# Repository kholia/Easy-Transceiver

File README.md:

### Easy-Transceiver

The whole design is modular, parametric (cost and others), field repairable,
and super extensible. It is almost trivial to add support for more `FSK digital
modes`.

The `Easy-Transceiver` hardware works with the native `Hybrid FT8 Radio`
Android app, and also with WSJT-X (running on RPi).

The `Easy-Transceiver` system can be built for around 3000 INR (~40 USD) or
less. We are working on reducing the cost to 2300 INR ;)

Author 1: LU2HES - https://github.com/agustinmartino

Author 2: Dhiru Kholia (VU3CER) - https://www.qrz.com/db/VU3CER/

TX chain:

RX chain (Easy-uSDX - optionally headless):

QSO(s):

QSOs over 15000 kms were made using this HW with PA150 (with around 37W ERP).

#### Notes

This will need a HF RF PA in most cases to be usable on the air.

UPDATE (January 2022): Check out our [cost-effective, and robust HF PA system](https://github.com/kholia/HF-PA-v5/).

#### Setup

- Use Python 3.10.x for maximum compatibility.

- Setup dependencies.

  `pip install -r requirements.txt`

#### T/R Switch

Check out our [cost-effective, and simple T/R switch design](https://github.com/kholia/Simple-TR-Switch/).

#### BCI Filter

Are you hearing broadcast AM signals in the background of the uSDX receiver? If
yes, a simple `BCI filter` can solve this problem easily enough.

Checkout the [RX BCI Filter](./HPF-BCI-Filter-RX) included in this repository.

#### BOM

- High Quality Female to Female Jumper Wire - 2500mA (Project Point)

- Female and male berg strip

- Arduino Nano v3 board - 450 INR - We will eliminate this requirement soon

- SN74CB3T3253DR (SOIC-16, Semikart) - ~200 INR

- Bunch of 100nF MLCC - 25 INR ('Emerging Technologies' Store -> ET)

- Bunch of 10nF MLCC - 10 INR

- Bunch of 1nF MLCC - 20 INR

- 4 x 470nF MLCC - 10 INR

- 1 x 1N5819 - 2 INR

- 1 x 1N4007 - 2 INR

- 1 x 7805 Linear Regulator - 15 INR

- 2 x 100uH inductor - 12 INR

- Si5351 Module - 470 INR (no delicate soldering required!)

  - Cheaper to get MS5351M from LCSC (in bulk for more experiments) - <= 100 INR

- Bunch of 10k resistors (MFR, ET / Project Point) - 25 INR

- Bunch of 1k resistors - 10 INR

- 1 x 1k 0.5W resistor - 5 INR

- 1 x 470 0.25W resistor - 5 INR

- 2 x 82k 0.25 resistor (MFR) - 5 INR

- 4 x 100 Ohm resistor (MFR) - 5 INR

- 1 x 3.5mm Stereo Socket ('PJ-307', https://www.electroncomponents.com/Stereo-Socket-3.5mm-connector-pcb) - 12 INR

- BCI Filter BOM - 2 x 2.2nF ceramic capacitor, 2 x 820pF (can be resistor shaped!), 3 * 2.2uH inductor axial

- 2 x SMA connectors (https://www.ktron.in/, SMA Straight - Female - Vertical Mount) - 50 INR

- ATmega328P (DIP-28) - 225 INR

- 20 MHz crystal - 10 INR

- LM4562NA - 220 INR (Semikart) OR NE5532AP (130 INR from Semikart, 30 INR locally from https://rarecomponents.com)

  The `NE5532` is widely faked - even https://www.electronicscomp.com/ sells a cheap knockoff!

  TIP: Get `TI make NE5532` from https://rarecomponents.com/.

- Misc: Copper clad board (glass epoxy one), Relimate male connectors + female
  cable, Male berg strip, Female-to-female dupont cables

  Get from https://www.electronicscomp.com/ and https://projectpoint.in/ shops.

- Total: Around 1500 to 1600 INR

#### BOM Sources

- https://robu.in/ (https://www.ktron.in/ has better pricing at times)

- https://www.electronicscomp.com/ (2.2uH Inductor)

- https://projectpoint.in/ (222 MLCC, 820pF MLCC)

- https://www.electroncomponents.com/2.2uh-inductor-inductance-coil (2.2uH Inductor)

#### Tips

Useful commands:

```
pacmd load-module module-null-sink sink_name=Virtual0
pacmd update-sink-proplist Virtual0 device.description=Virtual0
pacmd update-source-proplist Virtual0.monitor device.description=Virtual0
```

Use Gqrx and WSJT-X with a SDR device for initial frequency adjustment /
calibration. This is essential for WSPR functionality. FT8 is more
robust/tolerant of frequency deviations due to a much larger RX window.

#### References + Credits

- https://github.com/WB2CBA for the uSDX PCB

- https://github.com/kgoba/ft8_lib

- https://github.com/etherkit/JTEncode

- https://learn.adafruit.com/adafruit-si5351-clock-generator-breakout/wiring-and-test

- https://github.com/agustinmartino/wsjt_transceiver

- https://github.com/agustinmartino/wsjtx_transceiver_interface

- https://www.qrp-labs.com/synth/ms5351m.html

- https://github.com/kholia/Easy-Digital-Beacons-v1

- https://github.com/kholia/HF-Balcony-Antenna-System (fun!)

- https://github.com/kholia/SMPS-Noise-Filter

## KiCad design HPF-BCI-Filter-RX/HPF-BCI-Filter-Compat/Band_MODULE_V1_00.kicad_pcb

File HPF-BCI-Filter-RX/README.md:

Credits: https://www.youtube.com/watch?v=fgQenFJOjr4 (VK3YE)

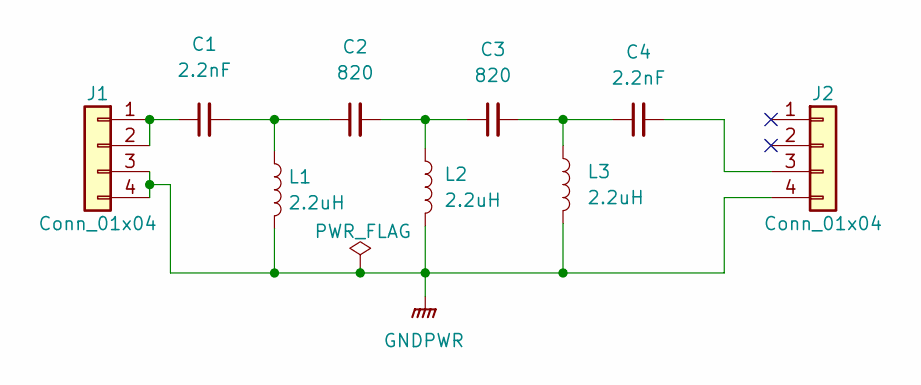
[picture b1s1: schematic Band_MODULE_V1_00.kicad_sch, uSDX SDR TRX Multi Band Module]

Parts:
C1, C4: 2.2nF; C_Disc_D3.0mm_W1.6mm_P2.50mm
C2, C3: 820; C_Disc_D3.0mm_W1.6mm_P2.50mm
J1, J2: Conn_01x04; PinHeader_1x4_P2.54mm_Drill1.02mm; MPN 0022232041; Digi-Key_PN WM4202-ND
L1, L2, L3: 2.2uH; R_Axial_DIN0204_L3.6mm_D1.6mm_P1.90mm_Vertical

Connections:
GNDPWR: J1.3, J1.4, J2.4, L1.2, L2.2, L3.2
unnamed: C1.1, J1.1, J1.2
unnamed: C1.2, C2.1, L1.1
unnamed: C2.2, C3.1, L2.1
unnamed: C3.2, C4.1, L3.1
unnamed: C4.2, J2.3

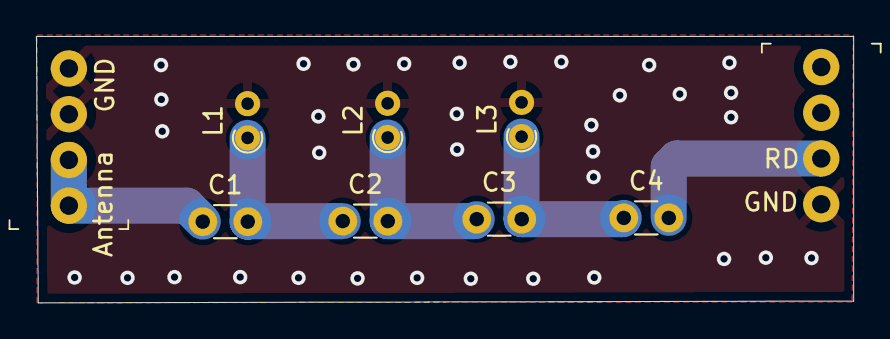
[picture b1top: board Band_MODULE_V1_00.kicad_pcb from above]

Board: 2 copper layers, 45.4 x 14.8 mm, 9 parts (0 on the bottom side), 6 nets.

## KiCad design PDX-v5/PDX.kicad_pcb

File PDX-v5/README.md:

#### PDX

A port of https://github.com/WB2CBA/ADX/ to Raspberry Pi Pico.

PDX-v3 is like v2 but is adapted for manufacturing @ JLCPCB.

PDX-v4 is like v3 with minor bugfixes.

PDX-v5 is like v4 with ADC-voltage-limiting circuit.

Bands covered: 80-meter to 15-meter.

FT8 is natively decoded on the Pico using the code from the following
repository:

https://github.com/kholia/pico_ft8_xcvr

The `PDX RX Block` when combined with the following project becomes a complete
5W (to 10W!) digital FT8 transceiver.

- https://github.com/kholia/HF-PA-v6/tree/master/HF-PA-Combined

  Solid 3W+ on 15m, 6W+ on 20m, 10W+ on 40m band. All @ 13.8v only!

  Set high gate bias (even 4.2v!) for IRF510 for clean linear output.

The live FT8 audio can also be decoded on PC / RPi / Android phone.

#### BOM Sources

International users can buy from Mouser and DigiKey.

Here are some local BOM sources I use:

- https://inkocean.in/ - CD2003 (Chinese clone which is known to work fine)

- https://www.electronicscomp.com/ (SMD resistors + SMD caps + THT inductors)

  - All SMD caps and resistors are 1206 sized

- https://www.ktron.in/ (SMA connectors)

- https://www.comkey.in/ - Branded SMD stuff

- https://rarecomponents.com/store/1002 - NXP 1N4148

- https://projectpoint.in/ - CDIL 7805, PJ307 Stereo Socket

- https://www.evelta.com/l7805-positive-voltage-regulator-1-5a-5v/ (alternate)

- https://robu.in/product/si5351a-i2c-8-khz-160-mhz-clock-generator-breakout-board-module/

- https://robu.in/product/raspberry-pi-pico/

- https://etstore.in/ - OEN MICRO RELAY 46-05-2C

#### Credits

- https://github.com/WB2CBA/ADX/

- https://www.qrz.com/DB/VU2BGS

#### References

- https://f5npv.wordpress.com/homebrew-ft8qrp-afp-fsk-trx/

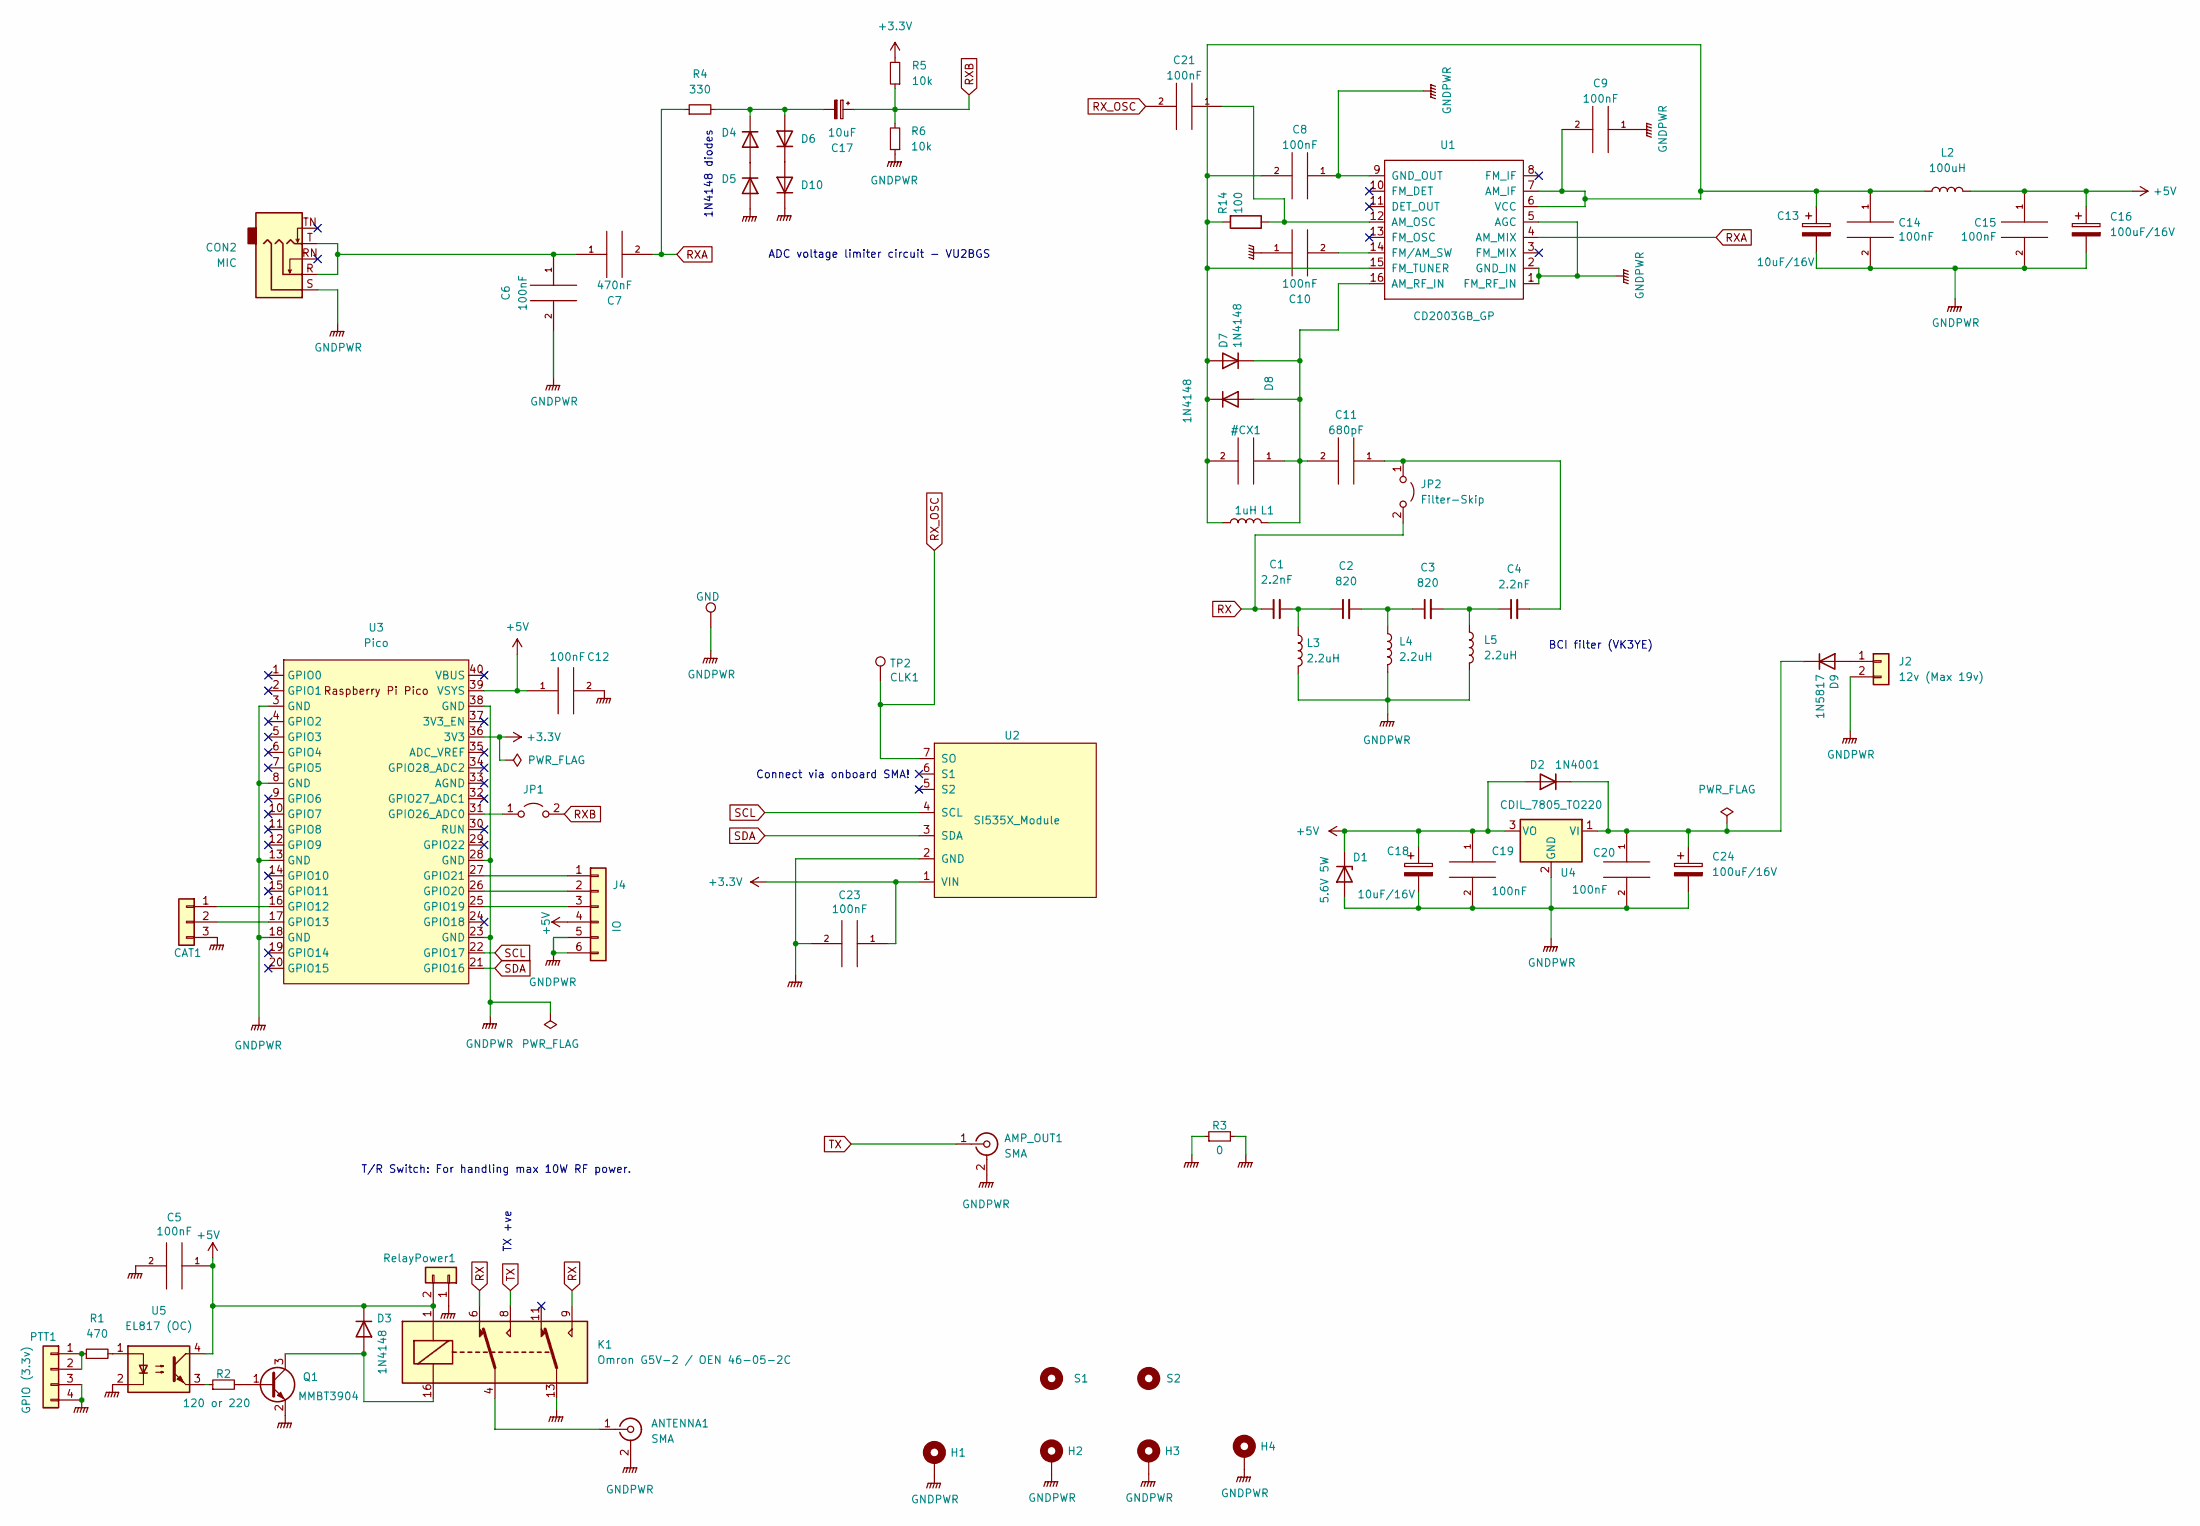
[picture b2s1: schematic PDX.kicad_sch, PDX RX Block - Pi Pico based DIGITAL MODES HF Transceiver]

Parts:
AMP_OUT1: SMA; SMA_Amphenol_901-144_Vertical
ANTENNA1: SMA; SMA_Amphenol_901-144_Vertical
C1, C4: 2.2nF; C_1206_3216Metric_Pad1.33x1.80mm_HandSolder
C2, C3: 820; C_1206_3216Metric_Pad1.33x1.80mm_HandSolder
C5, C6, C8, C9, C10, C12, C14, C15, C19, C20, C21, C23: 100nF; C_1206_3216Metric_Pad1.33x1.80mm_HandSolder
C7: 470nF; C_1206_3216Metric_Pad1.33x1.80mm_HandSolder
C11: 680pF; C_1206_3216Metric_Pad1.33x1.80mm_HandSolder
C13, C18: 10uF/16V; CP_Radial_D4.0mm_P2.00mm
C16, C24: 100uF/16V; CP_Radial_D4.0mm_P2.00mm
C17: 10uF; CP_Radial_D4.0mm_P2.00mm
CAT1: CAT; PinHeader_1x03_P2.54mm_Vertical
CON2: MIC; PJ-307
D1: 5.6V 5W; D_DO-15_P5.08mm_Vertical_KathodeUp
D2: 1N4001; D_SMA_Handsoldering
D3, D4, D5, D6, D7, D8, D10: 1N4148; D_DO-35_SOD27_P2.54mm_Vertical_KathodeUp
D9: 1N5817; D_A-405_P2.54mm_Vertical_KathodeUp
H1, H2, H3, H4: MountingHole_Pad; MountingHole_3.2mm_M3_ISO7380_Pad
J2: 12v (Max 19v); PinHeader_1x02_P2.54mm_Vertical
J4: IO; PinHeader_1x06_P2.54mm_Vertical
JP1: Jumper_2_Open; PinHeader_1x02_P2.54mm_Vertical
JP2: Filter-Skip; PinHeader_1x02_P2.54mm_Vertical
K1: Omron G5V-2 / OEN 46-05-2C; Relay_DPDT_Omron_G5V-2
L1: 1uH; L_Axial_L5.3mm_D2.2mm_P2.54mm_Vertical_Vishay_IM-1
L2: 100uH; L_Axial_L5.3mm_D2.2mm_P2.54mm_Vertical_Vishay_IM-1
L3, L4, L5: 2.2uH; L_Axial_L5.3mm_D2.2mm_P2.54mm_Vertical_Vishay_IM-1
PTT1: GPIO (3.3v); PinHeader_1x04_P2.54mm_Vertical
Q1: MMBT3904; SOT-23
R1: 470; R_1206_3216Metric_Pad1.30x1.75mm_HandSolder
R2: 120 or 220; R_1206_3216Metric_Pad1.30x1.75mm_HandSolder
R3: 0; R_1206_3216Metric_Pad1.30x1.75mm_HandSolder
R4: 330; R_1206_3216Metric_Pad1.30x1.75mm_HandSolder
R5, R6: 10k; R_Axial_DIN0207_L6.3mm_D2.5mm_P2.54mm_Vertical
R14: 100; R_1206_3216Metric_Pad1.30x1.75mm_HandSolder
RELAY_POWER1: RelayPower1; PinHeader_1x02_P2.54mm_Vertical
S1, S2: MountingHole; MountingHole_2.7mm_M2.5
TP2: CLK1; PinHeader_1x01_P2.54mm_Vertical
TP7: GND; PinHeader_1x01_P2.54mm_Vertical
U1: CD2003GB_GP; DIP-16_W7.62mm_Socket
U2: SI535X_Module; PinSocket_1x07_P2.54mm_Vertical
U3: Pico; RPi_Pico_SMD_TH
U4: CDIL_7805_TO220; TO-220-3_Vertical
U5: EL817 (OC); DIP-4_W7.62mm

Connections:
+3V3: C23.1, R5.2, U2.1 (VIN), U3.36 (3V3)
+5V: C5.1, C12.1, C15.1, C16.1, C18.1, C19.1, D1.1 (K), D2.2 (A), D3.1 (K), J4.4, K1.1, L2.2, RELAY_POWER1.2, U3.39 (VSYS), U4.3 (VO), U5.4
GNDPWR: AMP_OUT1.2 (Ext), ANTENNA1.2 (Ext), C5.2, C6.2, C8.1, C9.1, C10.1, C12.2, C13.2, C14.2, C15.2, C16.2, C18.2, C19.2, C20.2, C23.2, C24.2, CAT1.3, CON2.S, D1.2 (A), D5.2 (A), D10.1 (K), H1.1, H2.1, H3.1, H4.1, J2.2, J4.5, J4.6, K1.13, L3.2, L4.2, L5.2, PTT1.3, PTT1.4, Q1.2 (E), R3.1, R3.2, R6.1, RELAY_POWER1.1, TP7.1, U1.1 (FM_RF_IN), U1.2 (GND_IN), U1.5 (AGC), U1.9 (GND_OUT), U2.2 (GND), U3.3 (GND), U3.8 (GND), U3.13 (GND), U3.18 (GND), U3.23 (GND), U3.28 (GND), U3.38 (GND), U4.2 (GND), U5.2
unnamed: ANTENNA1.1 (In), K1.4
unnamed: C1.2, C2.1, L3.1
unnamed: C2.2, C3.1, L4.1
unnamed: C3.2, C4.1, L5.1
unnamed: C6.1, C7.1, CON2.R, CON2.T
unnamed: C10.2, U1.14 (FM/AM_SW)
unnamed: C4.2, C11.1, JP2.1 (A)
unnamed: C17.2, D4.1 (K), D6.2 (A), R4.2
unnamed: C20.1, C24.1, D2.1 (K), D9.1 (K), U4.1 (VI)
unnamed: C21.1, R14.1, U1.12 (AM_OSC)
unnamed: CAT1.1, U3.16 (GPIO12)
unnamed: CAT1.2, U3.17 (GPIO13)
unnamed: D3.2 (A), K1.16, Q1.3 (C)
unnamed: D4.2 (A), D5.1 (K)
unnamed: D9.2 (A), J2.1
unnamed: D6.1 (K), D10.2 (A)
unnamed: J4.1, U3.27 (GPIO21)
unnamed: J4.2, U3.26 (GPIO20)
unnamed: J4.3, U3.25 (GPIO19)
unnamed: JP1.1 (A), U3.31 (GPIO26_ADC0)
unnamed: PTT1.1, PTT1.2, R1.1
unnamed: Q1.1 (B), R2.2
unnamed: R1.2, U5.1
unnamed: R2.1, U5.3
RX: C1.1, JP2.2 (B), K1.6, K1.9
RXA: C7.2, R4.1, U1.4 (AM_MIX)
RXB: C17.1, JP1.2 (B), R5.1, R6.2
RX_OSC: C21.2, TP2.1, U2.7 (SO)
SCL: U2.4 (SCL), U3.22 (GPIO17)
SDA: U2.3 (SDA), U3.21 (GPIO16)
TX: AMP_OUT1.1 (In), K1.8

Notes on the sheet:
Connect via onboard SMA!
BCI filter (VK3YE)
1N4148 diodes
T/R Switch: For handling max 10W RF power.
ADC voltage limiter circuit - VU2BGS
TX +ve

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
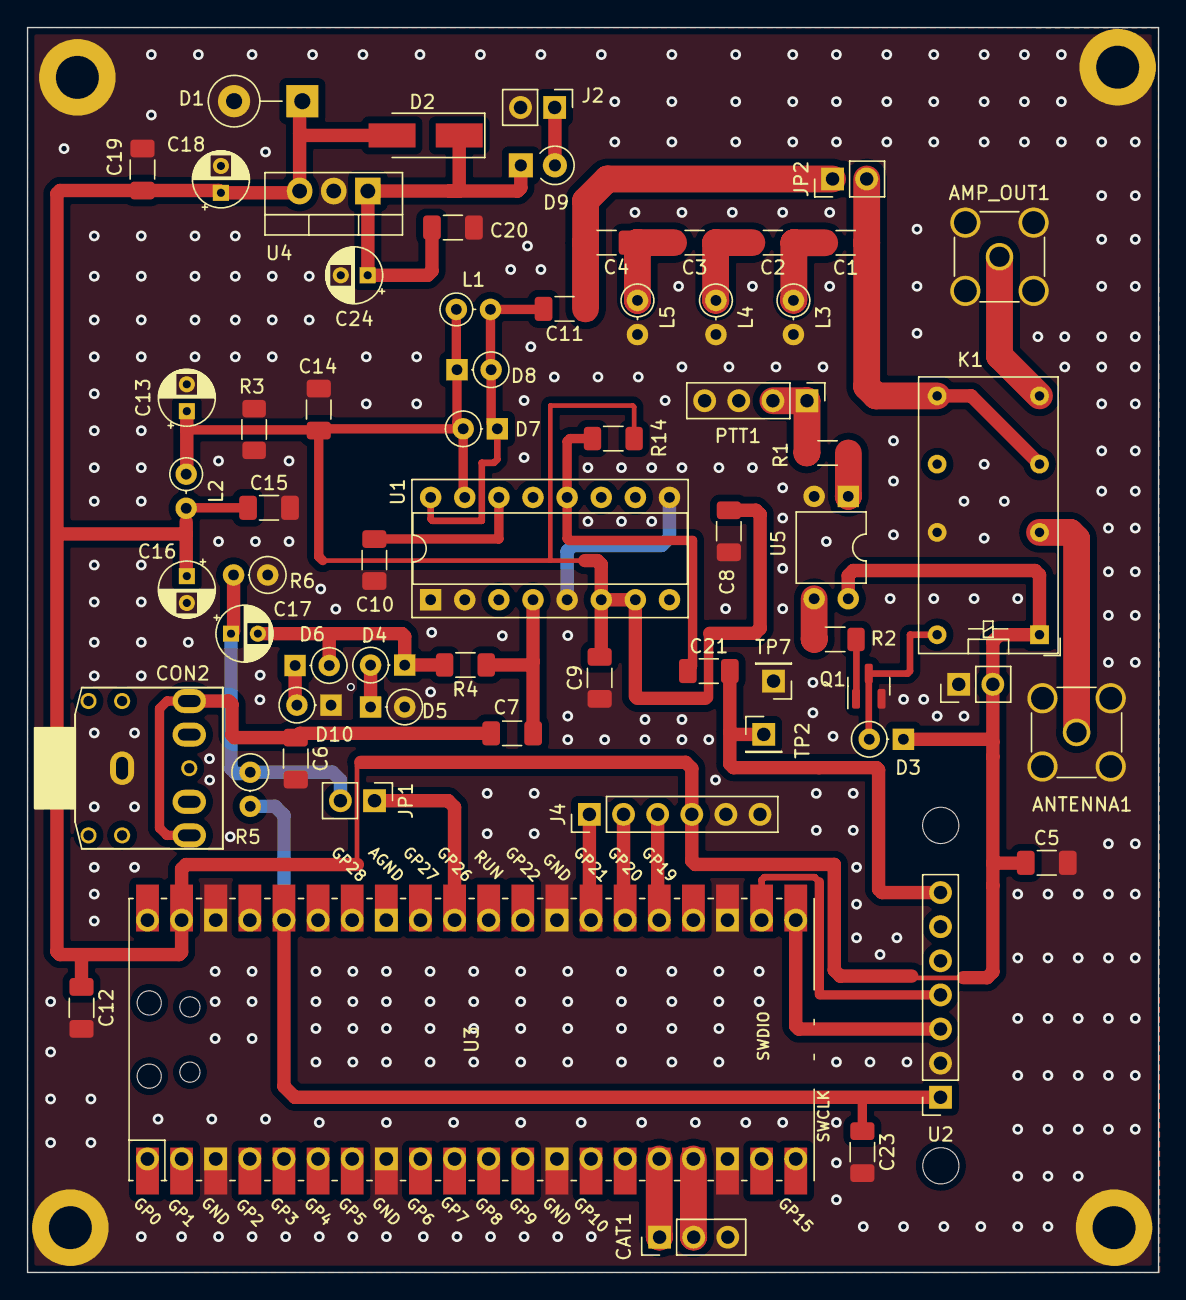
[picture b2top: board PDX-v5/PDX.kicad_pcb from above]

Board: 2 copper layers, 84.2 x 92.7 mm, 70 parts (0 on the bottom side), 36 nets.

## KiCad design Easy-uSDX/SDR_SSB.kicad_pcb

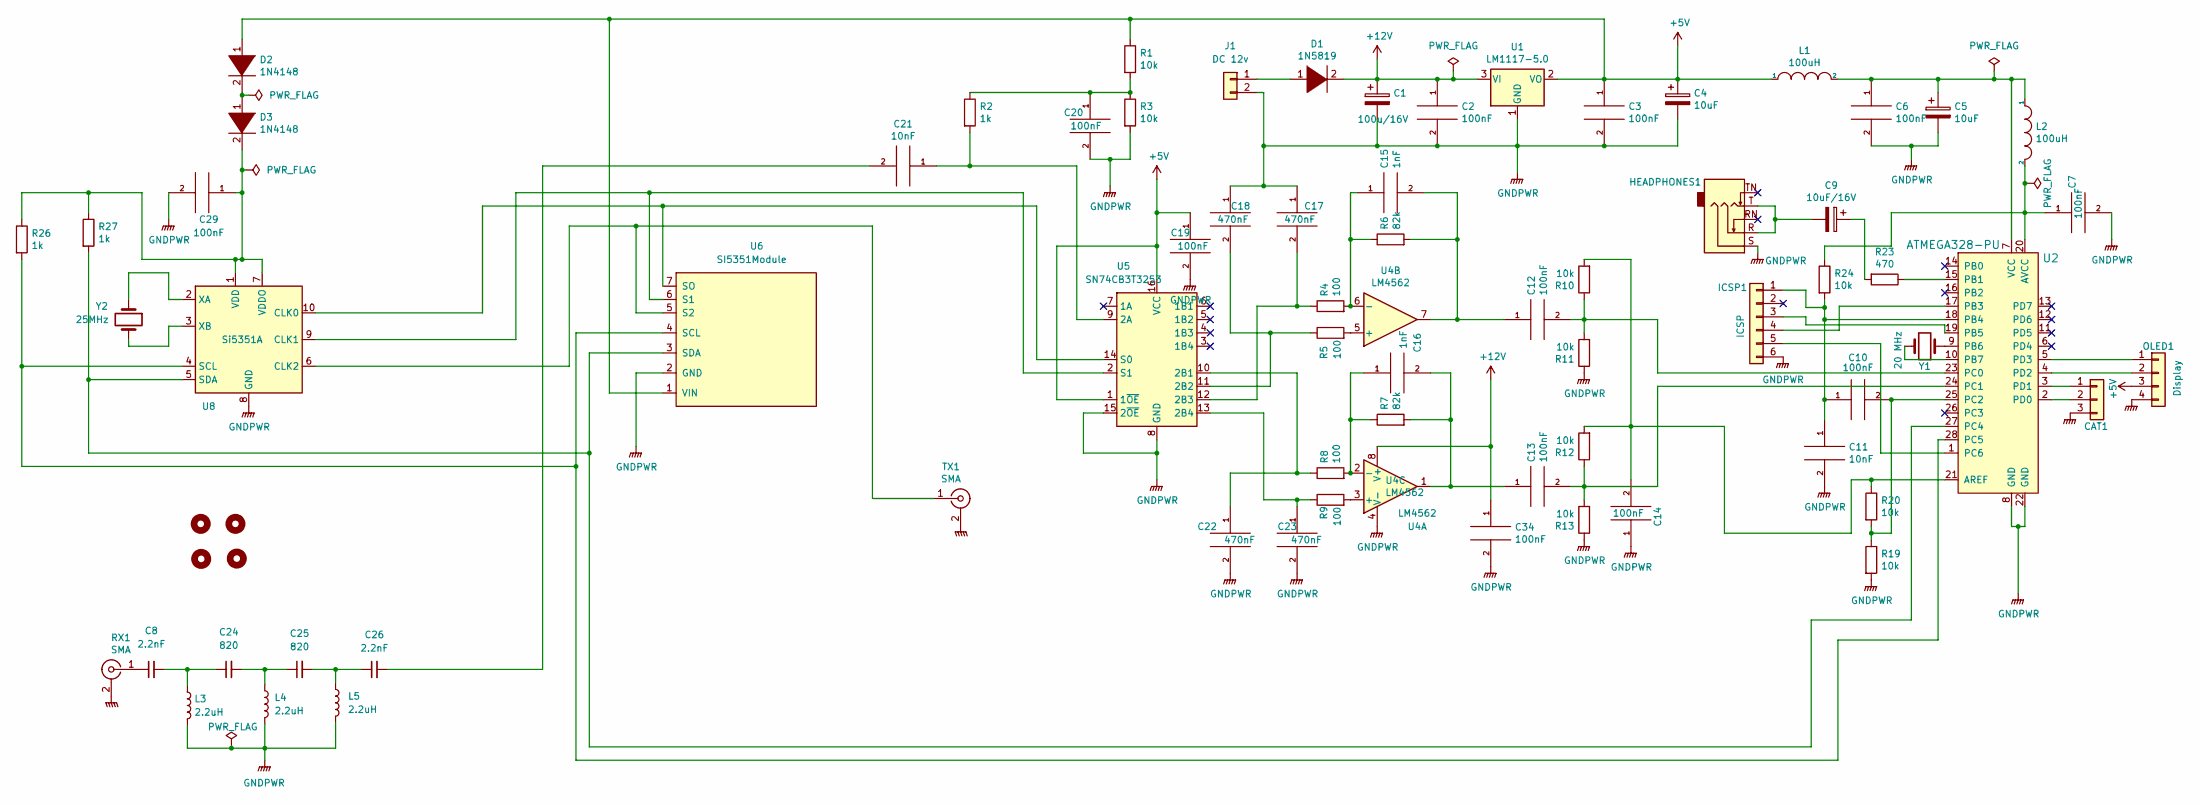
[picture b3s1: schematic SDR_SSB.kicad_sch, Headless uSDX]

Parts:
C1: 100u/16V; CP_Radial_D5.0mm_P2.50mm
C2, C3, C6, C7, C10, C12, C13, C14, C19, C20, C29, C34: 100nF; C_Disc_D3.0mm_W2.0mm_P2.50mm
C4, C5: 10uF; CP_Radial_D4.0mm_P2.00mm
C8, C26: 2.2nF; C_Disc_D3.0mm_W1.6mm_P2.50mm
C9: 10uF/16V; CP_Radial_D4.0mm_P2.00mm
C11, C21: 10nF; C_Disc_D3.0mm_W2.0mm_P2.50mm
C15, C16: 1nF; C_Disc_D3.0mm_W2.0mm_P2.50mm
C17, C18, C22, C23: 470nF; C_Disc_D3.0mm_W2.0mm_P2.50mm
C24, C25: 820; C_Disc_D3.0mm_W1.6mm_P2.50mm
CAT1: CAT; PinHeader_1x03_P2.54mm_Vertical
D1: 1N5819; D_A-405_P2.54mm_Vertical_AnodeUp
D2, D3: 1N4148; D_DO-35_SOD27_P2.54mm_Vertical_KathodeUp
H1, H2, H3, H4: MountingHole; MountingHole_2.2mm_M2
HEADPHONES1: AudioJack3_SwitchTR; PJ-307
ICSP1: ICSP; PinHeader_2x03_P2.54mm_Vertical
J1: DC 12v; PinHeader_1x02_P2.54mm_Vertical
L1, L2: 100uH; L_Axial_L5.3mm_D2.2mm_P2.54mm_Vertical_Vishay_IM-1
L3, L4, L5: 2.2uH; R_Axial_DIN0204_L3.6mm_D1.6mm_P1.90mm_Vertical
OLED1: Display; PinHeader_1x04_P2.54mm_Vertical
R1, R3, R10, R11, R12, R13, R19, R20, R24: 10k; R_Axial_DIN0204_L3.6mm_D1.6mm_P1.90mm_Vertical
R2, R26, R27: 1k; R_Axial_DIN0204_L3.6mm_D1.6mm_P1.90mm_Vertical
R4, R5, R8, R9: 100; R_Axial_DIN0204_L3.6mm_D1.6mm_P1.90mm_Vertical
R6, R7: 82k; R_Axial_DIN0204_L3.6mm_D1.6mm_P1.90mm_Vertical
R23: 470; R_Axial_DIN0204_L3.6mm_D1.6mm_P1.90mm_Vertical
RX1: SMA; SMA_Amphenol_901-144_Vertical
TX1: SMA; SMA_Amphenol_901-144_Vertical
U1: LM1117-5.0; SOT-223-3_TabPin2
U2: ATMEGA328-PU; DIP-28_W7.62mm_Socket_LongPads; MPN ATMEGA328-PU; Digi-Key_PN ATMEGA328-PU-ND
U4: LM4562; DIP-8_W7.62mm_LongPads
U5: SN74CB3T3253; SOIC-16_4.55x10.3mm_P1.27mm
U6: SI5351Module; SI5351 Module
U8: Si5351A; MSOP-10_3x3mm_P0.5mm
Y1: 20 MHz; Crystal_HC49-U_Vertical
Y2: 25MHz; Crystal_HC49-U_Vertical

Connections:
+5V: C3.1, C4.1, C19.1, D2.1 (K), L1.1, OLED1.3, R1.1, U1.2 (VO), U5.1 (1~OE), U5.16 (VCC), U6.1 (VIN)
+12V: C1.1, C2.1, C34.1, D1.2 (A), U1.3 (VI), U4.8 (V+)
GNDPWR: C1.2, C2.2, C3.2, C4.2, C5.2, C6.2, C7.2, C11.2, C14.1, C17.1, C18.1, C19.2, C20.2, C22.2, C23.2, C29.2, C34.2, CAT1.3, HEADPHONES1.S, ICSP1.6, J1.2, L3.2, L4.2, L5.2, OLED1.4, R3.2, R11.1, R13.1, R19.2, RX1.2 (Ext), TX1.2 (Ext), U1.1 (GND), U2.8 (GND), U2.22 (GND), U4.4 (V-), U5.8 (GND), U5.15 (2~OE), U6.2 (GND), U8.8 (GND)
unnamed: C5.1, C6.1, L1.2, L2.1, U2.7 (VCC)
unnamed: C7.1, L2.2, R24.1, U2.20 (AVCC)
unnamed: C8.1, RX1.1 (In)
unnamed: C9.1, R23.2
unnamed: C9.2, HEADPHONES1.R, HEADPHONES1.T
unnamed: C10.1, C11.1, ICSP1.1, R24.2, U2.18 (PB4)
unnamed: C10.2, R19.1, R20.2, U2.25 (PC2)
unnamed: C12.1, C15.2, R6.2, U4.7
unnamed: C12.2, R10.1, R11.2, U2.23 (PC0)
unnamed: C13.1, C16.2, R7.2, U4.1
unnamed: C13.2, R12.1, R13.2, U2.24 (PC1)
unnamed: C14.2, R10.2, R12.2, R20.1, U2.21 (AREF)
unnamed: C15.1, R4.2, R6.1, U4.6 (-)
unnamed: C16.1, R7.1, R8.2, U4.2 (-)
unnamed: C17.2, R4.1, U5.12 (2B3)
unnamed: C18.2, R5.1, U5.11 (2B2)
unnamed: C20.1, R1.2, R2.1, R3.1
unnamed: C21.1, R2.2, U5.9 (2A)
unnamed: C21.2, C26.2
unnamed: C22.1, R8.1, U5.10 (2B1)
unnamed: C23.1, R9.1, U5.13 (2B4)
unnamed: C8.2, C24.1, L3.1
unnamed: C24.2, C25.1, L4.1
unnamed: C25.2, C26.1, L5.1
unnamed: C29.1, D3.2 (A), R26.1, R27.1, U8.1 (VDD), U8.7 (VDDO)
unnamed: CAT1.1, U2.3 (PD1)
unnamed: CAT1.2, U2.2 (PD0)
unnamed: D1.1 (K), J1.1
unnamed: D2.2 (A), D3.1 (K)
unnamed: ICSP1.3, U2.19 (PB5)
unnamed: ICSP1.4, U2.17 (PB3)
unnamed: ICSP1.5, U2.1 (PC6)
unnamed: OLED1.1, U2.5 (PD3)
unnamed: OLED1.2, U2.4 (PD2)
unnamed: R5.2, U4.5 (+)
unnamed: R9.2, U4.3 (+)
unnamed: R23.1, U2.15 (PB1)
unnamed: R26.2, U2.28 (PC5), U6.4 (SCL), U8.4 (SCL)
unnamed: R27.2, U2.27 (PC4), U6.3 (SDA), U8.5 (SDA)
unnamed: TX1.1 (In), U6.5 (S2), U8.6 (CLK2)
unnamed: U2.9 (PB6), Y1.1
unnamed: U2.10 (PB7), Y1.2
unnamed: U5.2 (S1), U6.6 (S1), U8.9 (CLK1)
unnamed: U5.14 (S0), U6.7 (SO), U8.10 (CLK0)
unnamed: U8.2 (XA), Y2.1
unnamed: U8.3 (XB), Y2.2

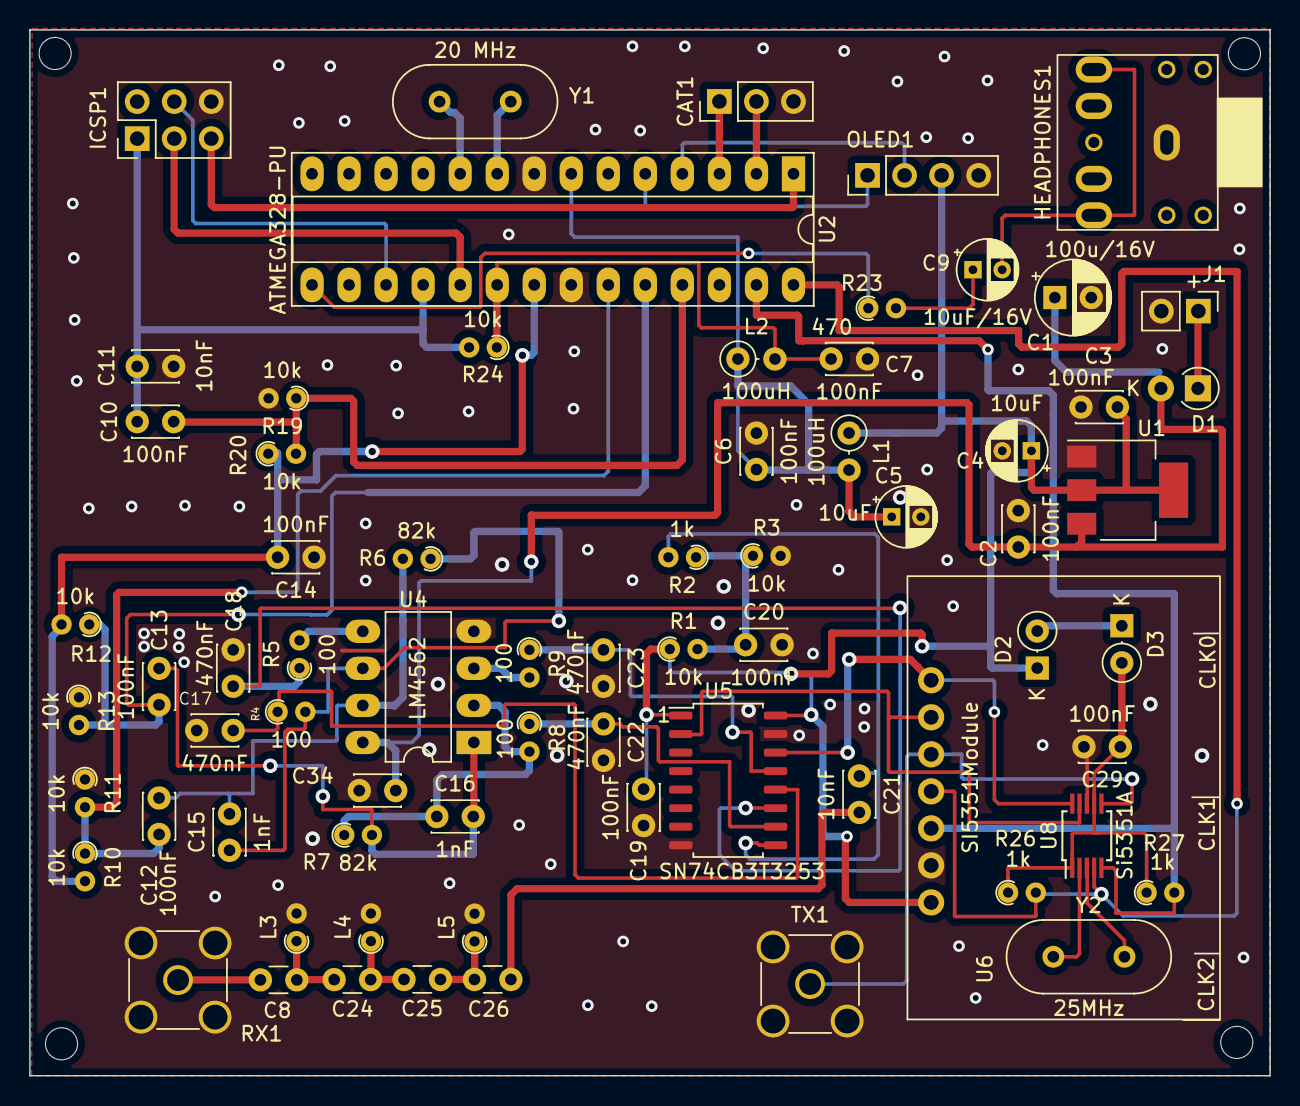
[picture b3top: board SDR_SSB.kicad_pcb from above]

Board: 2 copper layers, 85.1 x 71.7 mm, 74 parts (0 on the bottom side), 49 nets.

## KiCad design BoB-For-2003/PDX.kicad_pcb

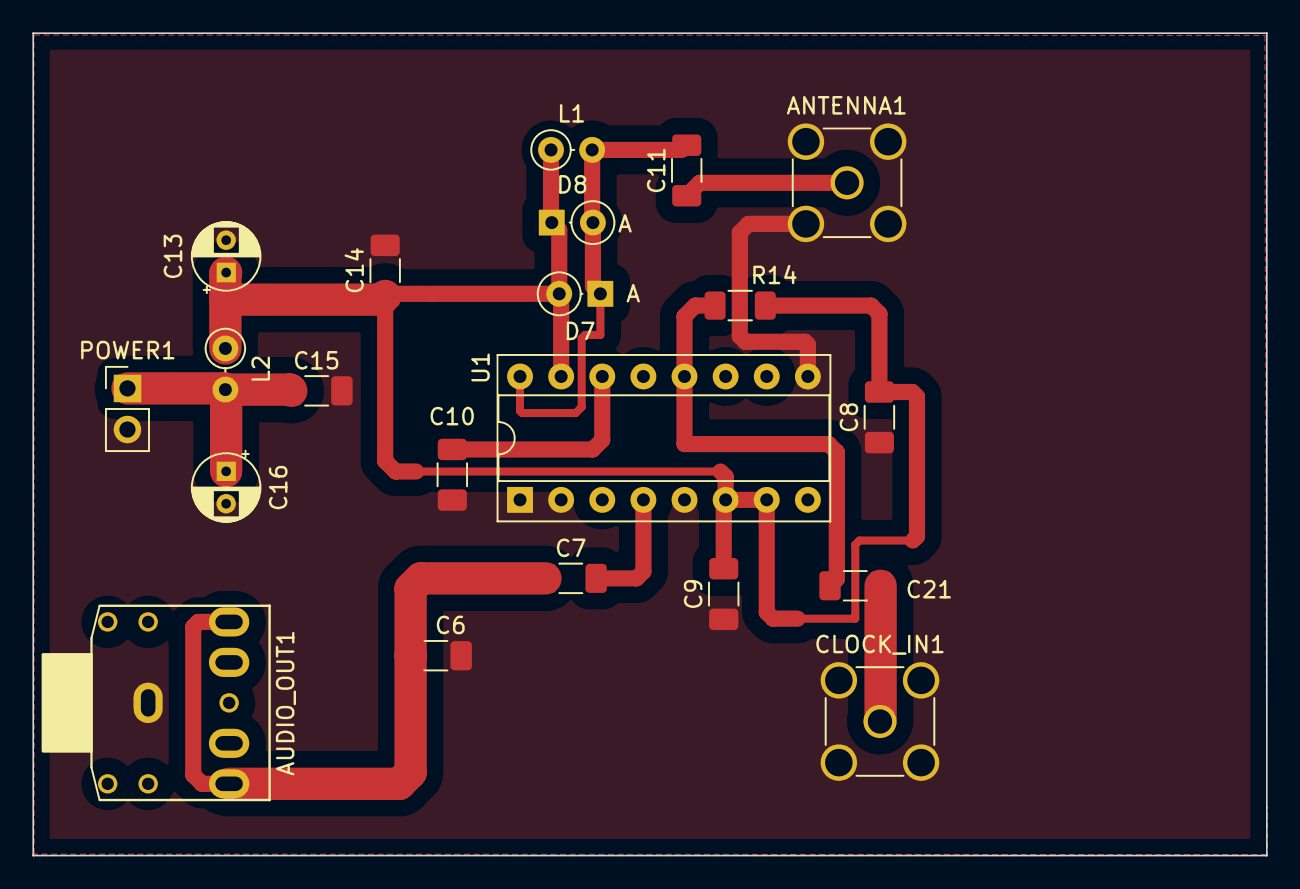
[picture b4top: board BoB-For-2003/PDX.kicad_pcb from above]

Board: 2 copper layers, 76.2 x 50.8 mm, 21 parts (0 on the bottom side), 10 nets.

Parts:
ANTENNA1: RX_INPUT; SMA_Amphenol_901-144_Vertical
AUDIO_OUT1: MIC; PJ-307
C6, C8, C9, C10, C14, C15, C21: 100nF; C_1206_3216Metric_Pad1.33x1.80mm_HandSolder
C7: 470nF; C_1206_3216Metric_Pad1.33x1.80mm_HandSolder
C11: 680pF; C_1206_3216Metric_Pad1.33x1.80mm_HandSolder
C13: 10uF/16V; CP_Radial_D4.0mm_P2.00mm
C16: 100uF/16V; CP_Radial_D4.0mm_P2.00mm
CLOCK_IN1: Conn_Coaxial; SMA_Amphenol_901-144_Vertical
D7, D8: 1N4148; D_DO-35_SOD27_P2.54mm_Vertical_KathodeUp
L1: 1uH; L_Axial_L5.3mm_D2.2mm_P2.54mm_Vertical_Vishay_IM-1
L2: 100uH; L_Axial_L5.3mm_D2.2mm_P2.54mm_Vertical_Vishay_IM-1
POWER1: Conn_01x02; PinHeader_1x02_P2.54mm_Vertical
R14: 100; R_1206_3216Metric_Pad1.30x1.75mm_HandSolder
U1: CD2003GB_GP; DIP-16_W7.62mm_Socket

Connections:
+5V: C15.1, C16.1, L2.2, POWER1.1
GNDPWR: ANTENNA1.2 (Ext), AUDIO_OUT1.S, C6.2, C8.1, C9.1, C10.1, C13.2, C14.2, C15.2, C16.2, CLOCK_IN1.2 (Ext), POWER1.2, U1.1 (FM_RF_IN), U1.2 (GND_IN), U1.5 (AGC), U1.9 (GND_OUT)
unnamed: C10.2, U1.14 (FM/AM_SW)
unnamed: ANTENNA1.1 (In), C11.1
unnamed: C11.2, D7.1 (K), D8.2 (A), L1.2, U1.16 (AM_RF_IN)
unnamed: C8.2, C9.2, C13.1, C14.1, D7.2 (A), D8.1 (K), L1.1, L2.1, R14.2, U1.6 (VCC), U1.7 (AM_IF), U1.15 (FM_TUNER)
unnamed: C21.1, R14.1, U1.12 (AM_OSC)
RXA: C7.2, U1.4 (AM_MIX)
RXB: AUDIO_OUT1.R, AUDIO_OUT1.T, C6.1, C7.1
RX_OSC: C21.2, CLOCK_IN1.1 (In)
